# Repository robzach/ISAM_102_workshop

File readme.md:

# ISAM 102 Workshop

This repository contains files relevant to the ISAM 102 Workshop, offered as part of the [ISAM (International Symposium on Academic Makerspaces)](https://isam2026.hemi-makers.org/) conference hosted at Rice University in Houston, TX on October 11, 2026.

## Key links

* [The workshop slide deck](https://docs.google.com/presentation/d/1ssW1kLEdIV6doIdHSlkZcHQL9aKUUs60g7Cv7FatsbY/edit?usp=sharing) gives a good overview of the project
* [Bill of materials](https://docs.google.com/spreadsheets/d/1SMaYd1W7RdJwxCUgwH0dufXo5XOK3xKtL_PFmABzuK0/edit?usp=sharing) including costs and sources (also linked below)
* Most design files are contained in this repo, organized by the design software used. Our Fusion designs are viewable (and downloadable) below:
  + [Chassis base](https://a360.co/3UgWDdf)
  + [3d-printed 36 tooth gear](https://a360.co/4jhnJLu)
  + [Snap-fit rings](https://a360.co/4AZ4c8O)
  + [Scotty dog](https://a360.co/4AZ4c8O)
  + [Tail wagger](https://a360.co/4dzIVbR)
  + [Gear arrangement sketch](https://a360.co/4dyHuKM)

## Workshop printouts

document | document source (copy and modify) | PDF
--- | --- | ---
Bill of Materials (BOM) handout | [Google Sheets BOM](https://docs.google.com/spreadsheets/d/1SMaYd1W7RdJwxCUgwH0dufXo5XOK3xKtL_PFmABzuK0/edit?usp=sharing); [draw.ioRef.org bolt lengths and simplified schematic](https://drive.google.com/file/d/1bY67-kRYnys0FUMiLNIe3cIf9ZiAv4Ug/view?usp=sharing) | [PDF](<workshop printouts/ISAM 102 BOM, bolt length chart, reference schematic.pdf>)
More detailed schematic | [draw.ioRef.org source](https://drive.google.com/file/d/195w9GBgT-5P33YUQ5w68HSQIwB7dRBu5/view?usp=sharing) | [PDF](<workshop printouts/big schematic.pdf>)
Blown-up breadboard photo | | [PDF](<workshop printouts/blown-up circuit photo.pdf>)
Order of construction (used by organizers) | [Google Docs source](https://docs.google.com/document/d/1IrMTVL7Qs2d7-0CwFLS_1lchCKMhTqDqpBA163-08qU/edit?usp=sharing) | [PDF](<workshop printouts/Order of construction.pdf>)

## Free and open-source software mentioned in the workshop

### CAD and mechanical simulation

* [OpenSCAD](https://openscad.org/), "The programmer's solid 3D CAD modeller," compiles your software-style source code into geometry. It allows for highly parameterized drawings, and can be called from the command line.
* [LibreCAD](https://librecad.org/) is a DXF-native drawing application designed for producing engineering drawings in two dimensions. 
* [SolveSpace](https://solvespace.com/) has an interface that looks like it's from about 1989, but but that's just part of its charm; it can draw in two and three dimensions including using parameters if you wish, and also can simulate kinematic linkages as we demonstrated.
* [Inkscape]() is a vector-drawing application suitable for opening DXFs and SVGs from CAD software, to add final touches before sending to a lasercutter (or drawing from scratch). The "Hershey text" extension is great for lasercutting.
* [Boxes.py](https://boxes.hackerspace-bamberg.de/?language=en) is a very useful compendium of parametric lasercuttable objects.

### Schematic capture and circuit simulation

* [KiCAD](https://kicad.org/) is a very fully-featured circuit and PCB design suite, including simulation. We used it to create our CNC milled circuit and industrially-fabbed PCB.
* [Falstad's circuit simulator]() written by Paul Falstad, actually shows current flowing through the wires (excellent for understanding what's going on in an active circuit), and runs entirely in the browser. It also has a fabulous range of sample circuits under the "circuits" menu.
* [The ioRef schematic and system drawing tool](https://draw.ioref.org) is a customized version of [draw.io](https://www.drawio.com/), with block-level and schematic-level electronic components meant to make it easy for beginners to draw clear, legible circuits.

### Microcontroller wiring and programming

* [Breadboard secrets](https://cmuiii.ai/examples/wiring) is a simple page to help students understand the relationship between the breadboard and the circuit represented on it. It was written with AI assistance by faculty from Carnegie Mellon's Integrated Innovation Institute.
* [Arduino code](https://cmuiii.ai/examples/code) is another simple demo visualizing the actual electronics results of running each line of an Arduino sketch, also from CMU's III.

## Workshop leaders

* [Robert Zacharias](https://www.andrew.cmu.edu/user/rzachari), Associate Teaching Professor, IDeATe (Integrative Design, Arts, and Technology) and Entertainment Technology Center, Carnegie Mellon University
* [Bill Nace](https://www.ece.cmu.edu/directory/bios/nace-bill.html), Teaching Professor, Electrical and Computer Engineering, Carnegie Mellon University

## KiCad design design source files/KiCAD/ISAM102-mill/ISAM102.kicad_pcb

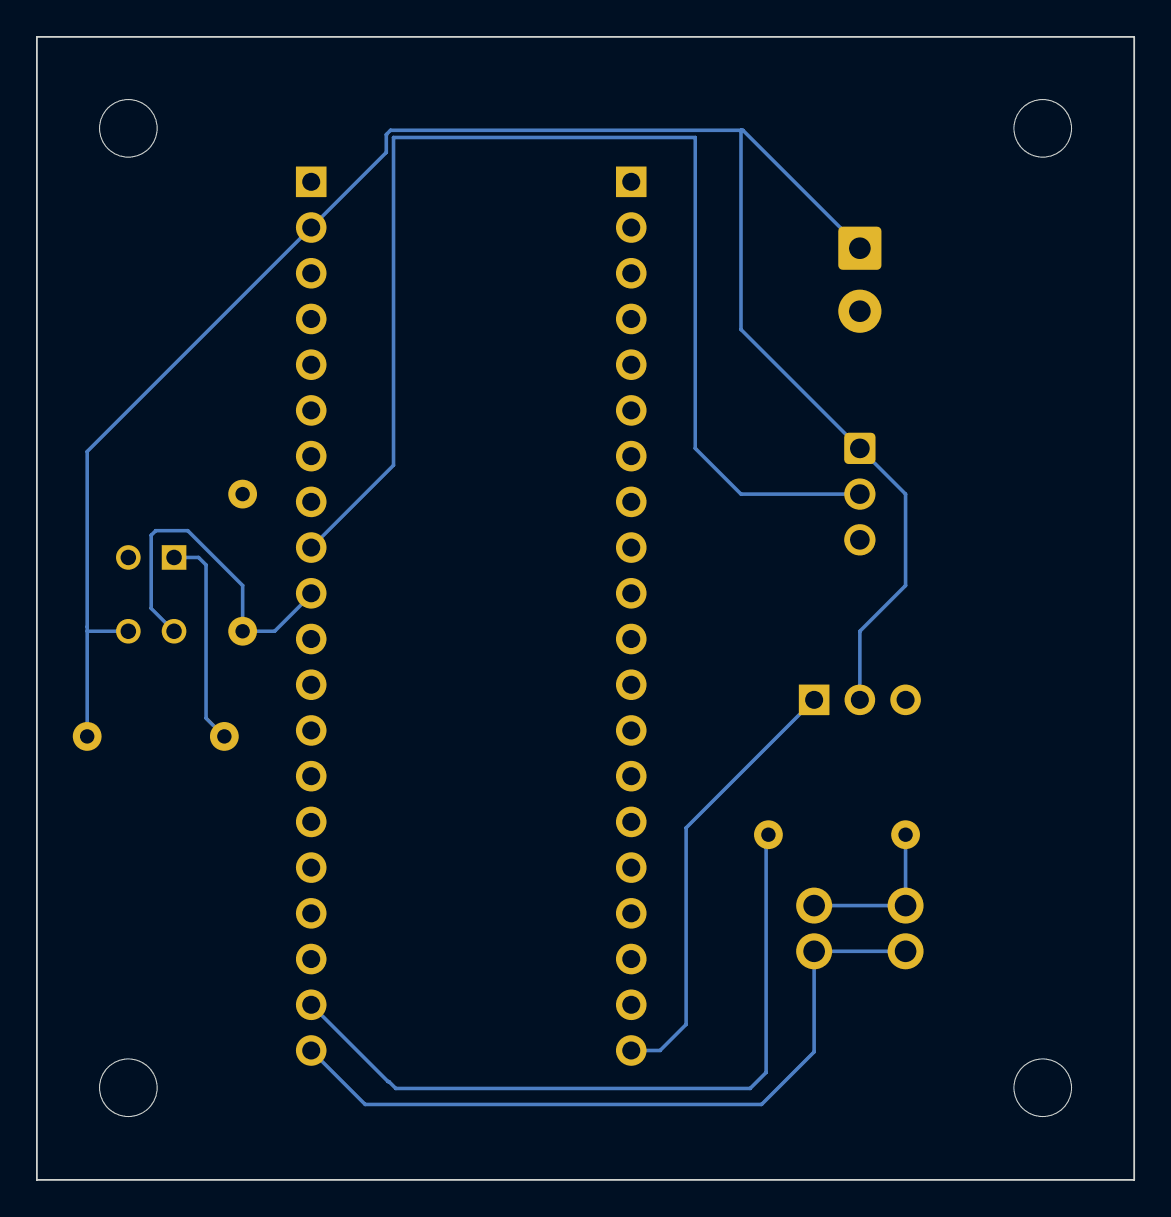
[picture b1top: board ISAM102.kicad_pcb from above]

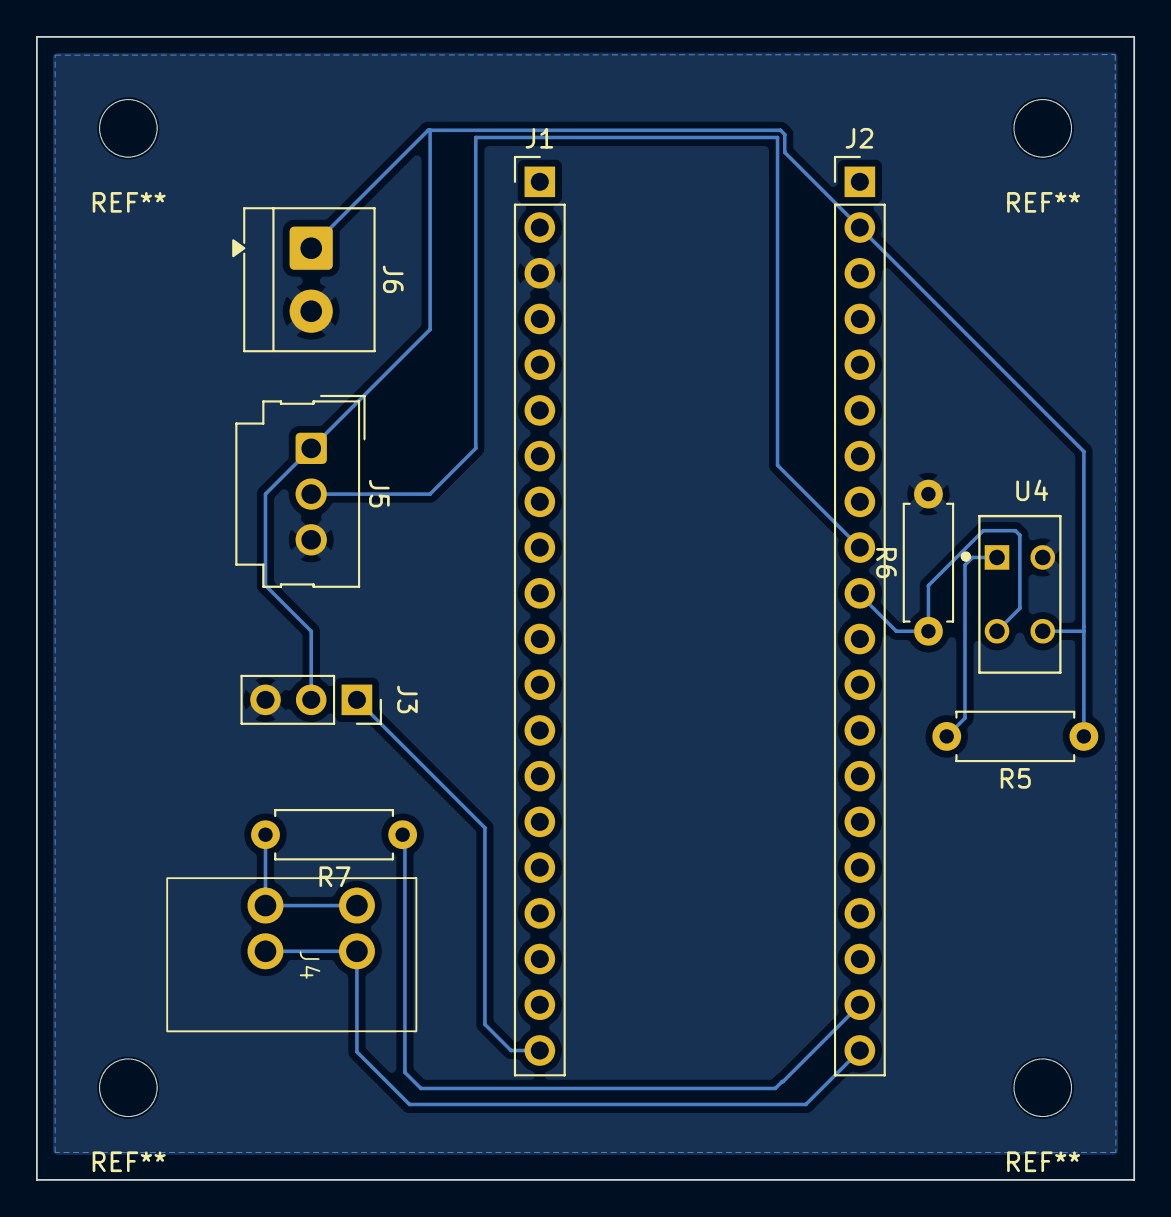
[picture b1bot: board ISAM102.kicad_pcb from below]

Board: 2 copper layers, 61.0 x 63.5 mm, 10 parts (10 on the bottom side), 9 nets.

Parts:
J1, J2: Conn_01x20; PinHeader_1x20_P2.54mm_Vertical
J3: Conn_01x03_Socket; PinSocket_1x03_P2.54mm_Vertical
J4: 1-2834016-2; Spring_Terminal_Side_Entry_two_terminal_P2.54x5.08mm
J5: 70543-0037; Molex_SL_171971-0003_1x03_P2.54mm_Vertical
J6: Screw_Terminal_01x02; TerminalBlock_4Ucon_1x02_P3.50mm_Horizontal
R5: 220Ω; R_Axial_DIN0207_L6.3mm_D2.5mm_P7.62mm_Horizontal
R6: 5.6kΩ; R_Axial_DIN0207_L6.3mm_D2.5mm_P7.62mm_Horizontal
R7: 10Ω; R_Axial_DIN0207_L6.3mm_D2.5mm_P7.62mm_Horizontal
U4: LTH-1550-01; PHOTOINTERRUPTER_LTH-1550-01

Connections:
/PCB connections/GPIO15: J1.20, J3.1
/PCB connections/GPIO16: J2.20, J4.3, J4.4
/PCB connections/GPIO17: J2.19, R7.1
/PCB connections/GPIO26_ADC0: J2.10, R6.1, U4.2
/PCB connections/GPIO27_ADC1: J2.9, J5.2
GND: J1.3, J3.3, J5.3, J6.2, R6.2, U4.4
unnamed: J4.1, J4.2, R7.2
unnamed: R5.2, U4.1
VCC: J2.2, J3.2, J5.1, J6.1, R5.1, U4.3

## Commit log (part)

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2023-10-12 link malformation
2023-10-12 new Scotty driver version
2023-10-12 add BOM link
2023-10-15 modified square clamp design to have triangular rather than rectangular cutout; added properly formed parameters after some variables to allow for easier use of "customizer" tool
2023-10-16 add schematics
2023-10-16 added back smaller rectangular cut to allow for clamping area to flex without tearing away from base
2023-10-16 initial batch of photos
2023-10-16 version for testing 10-16-23
2023-10-16 Added Gears weblink
2023-10-17 Images and Corel Draw files
2023-10-18 adds simple autoranging feature, light-blinking feedback, and Arduino Pro Micro pin mapping
2023-10-18 move servo to pin 9
2023-10-18 update some links
2023-10-18 more process images
2023-10-18 add Thingiverse link
2023-10-18 change minimum motor speed to 90 so it fully stops
2023-10-18 Fusion360 links in readme
2023-10-18 add breadboard photos
2024-07-30 updates for 2024
2024-08-01 variety of geometry updates, as well as more user-settable parameters
2024-08-01 adjusting links
2024-08-01 add Robin's institutional affiliation
2024-08-01 update Customizer headings, etc.
2024-08-07 optimizations for 3d printing and other design tweaks
2024-08-07 initial commit of RasPi Pico files
2024-08-07 Rename 10-16-23 cutting 1:4" shaft.JPG to 10-16-23 cutting 0.25 in shaft.JPG because the colon and quote marks aren't legal file name characters on Windows
2024-08-07 Update readme.md
    Updated Robin's title
2024-08-16 updates to blink external LED and read potentiometer to set minimum speed
2024-09-08 update to v5 parameters, used in printing for project, and also add embossed text to customizer
2024-09-11 refactored, pins shifted around, and full introductory comment block added
2024-09-11 these servos run the other way, so changed the max angle to 0º
2024-09-11 clearing out 2023 material
2024-09-11 update links
2024-09-11 adding production files labeled with part numbers
2024-09-12 placeholder documentation readme
2025-08-03 updated some links and details, filled in others with TODOs
2025-08-03 added 2nd LED output pin (for bi-color LED)
2025-08-06 added some links
2025-08-06 I think I finally understand how parentheses work
2025-08-08 Add Fusion links
2025-09-17 add missing STLs that came from ancillary Fusion drawings
2025-09-17 add clamping and non-clamping hub 3mf files
2025-09-17 adding knob folder with all the variant knobs we printed as well as the OpenSCAD source (plus shell script for generating a folder full of variants; see the top comment block of CustomizableKnob.scad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
2026-05-28 update to v6, adjusting default clamping diameter and tweaking customizer clamping nut values
2026-05-28 36 Tooth gear moved closer to acrylic wall
2026-05-31 Converted 12 tooth gear to SVG (Horray for Shaper Utilities)
2026-06-09 change all default values to v7 clamp design; fix slightly-too-small hex nut cutouts
2026-06-09 Increase default clamping nut clearance from 0.2 to 0.5 to match v7
2026-06-23 add customizer option to fix mounting hole placement
